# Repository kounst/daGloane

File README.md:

daGloane
========

daGloane is a quadcopter with a takeoff mass of less than 30grams

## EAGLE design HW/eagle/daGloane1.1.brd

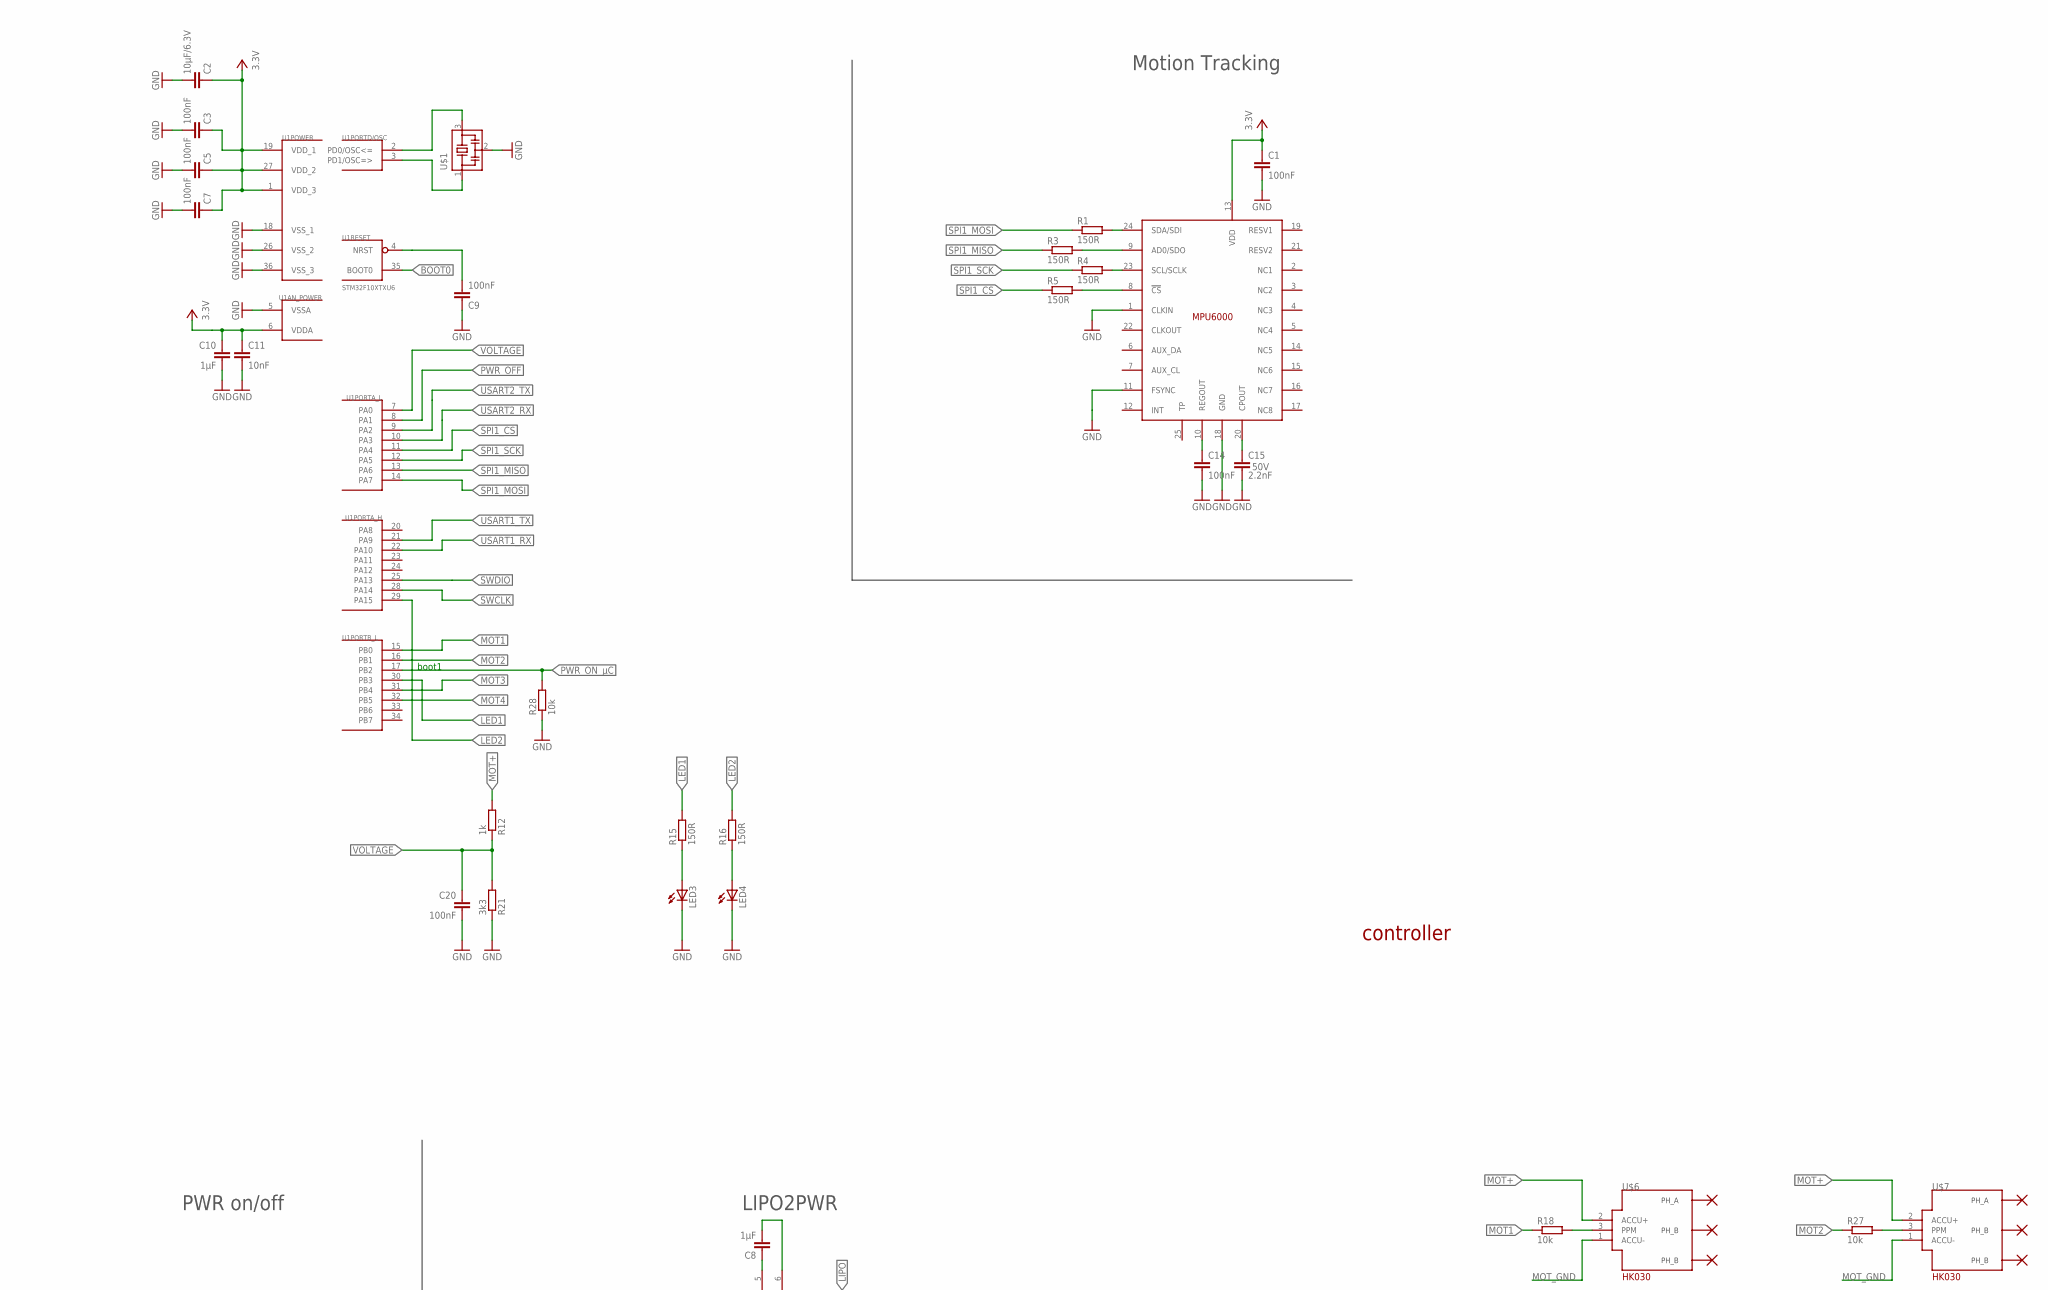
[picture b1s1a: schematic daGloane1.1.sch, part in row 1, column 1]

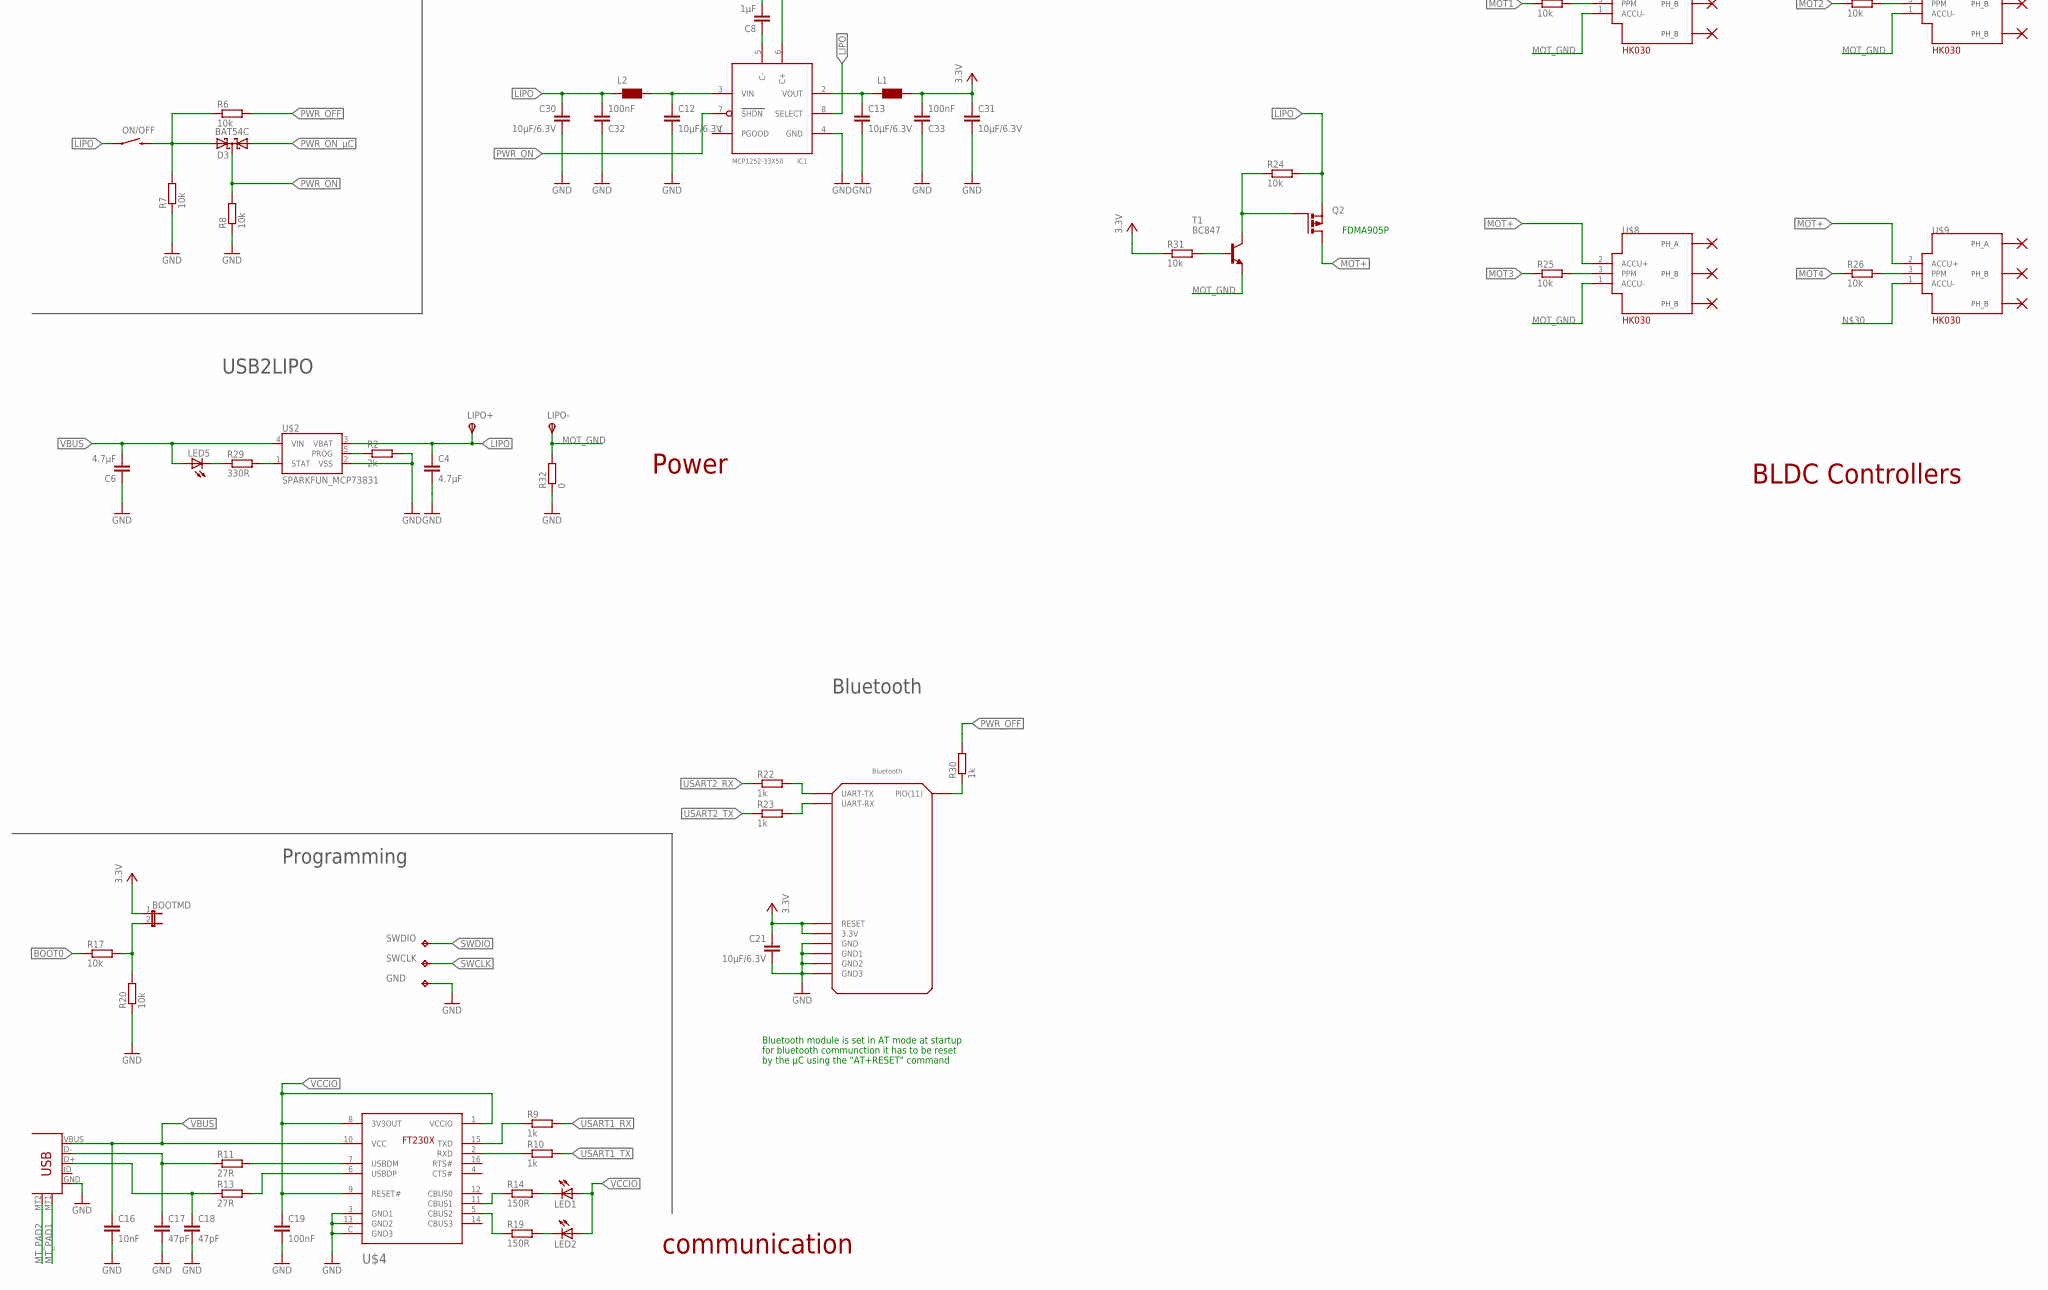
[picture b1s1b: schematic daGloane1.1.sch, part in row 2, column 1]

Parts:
BOOTMD: JUMPER-2; 1X02_50MIL
C1, C3, C5, C7, C9, C14, C19, C20, C32, C33: 100nF; C0603
C2, C12, C13, C21, C30, C31: 10µF/6.3V; C0805
C4, C6: 4.7µF; C0603
C8, C10: 1µF; C0603
C11, C16: 10nF; C0603
C15: 2.2nF; C0603; VOLTAGE 50V
C17, C18: 47pF; C0603
D3: BAT54C; SOT23
GND: TESTPAD_TPB1,27; TESTPAD_B1,27
IC1: MCP1252-33X50; MSOP8
L1, L2: WUERTH-ELEKTRONIK_WE-KI_0805_B
LED1, LED2, LED3, LED4, LED5: LEDCHIPLED_0603; CHIPLED_0603
LIPO+: TPSPAD1-13; P1-13
LIPO-: TPSPAD1-13; P1-13
ON/OFF: SWITCH-MOMENTARY-2SMD; TACTILE_SWITCH_SMD
Q2: P-MOSFET-SO8; MICROFET2X2
R1, R3, R4, R5, R14, R15, R16, R19: 150R; R0603
R2: 2k; R0603
R6, R7, R8, R17, R18, R20, R24, R25, R26, R27, R28, R31: 10k; R0603
R9, R10, R12, R22, R23, R30: 1k; R0603
R11, R13: 27R; R0603
R21: 3k3; R0603
R29: 330R; R0603
R32: 0; R0603
SWCLK: TESTPAD_TPB1,27; TESTPAD_B1,27
SWDIO: TESTPAD_TPB1,27; TESTPAD_B1,27
T1: BC847; SOT23
U1: STM32F10XTXU6; VFQFPN36
U$1: MURATA-FILTER_CSTCE__G
U$2: SPARKFUN_MCP73831; SPARKFUN_SOT23-5
U$3: MPU6000
U$4: SERIAL_FT230XQ; SERIAL_QFN4X4-16
U$5: BLUETOOTH_REDUCED
U$6, U$7, U$8, U$9: 3A_BLDC_CONTROLLER
X2: USB_MICROB_PLUG_MT; SPARKFUN-CONNECTORS_USB-MICROB

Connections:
BOOT0: R17.1, U1.35 (BOOT0)
D+: C18.1, R13.1, X2.D+
D-: C17.1, R11.1, X2.D-
GND: C1.2, C2.2, C3.2, C4.2, C5.2, C6.1, C7.2, C9.1, C10.2, C11.2, C12.2, C13.2, C14.2, C15.2, C16.2, C17.2, C18.2, C19.2, C20.2, C21.2, C30.2, C31.2, C32.1, C33.1, GND.PP, IC1.4 (GND), LED3.C, LED4.C, R2.2, R7.1, R8.1, R20.1, R21.1, R28.1, R32.1, U1.5 (VSSA), U1.18 (VSS_1), U1.26 (VSS_2), U1.36 (VSS_3), U$1.2, U$2.2 (VSS), U$3.1 (CLKIN), U$3.11 (FSYNC), U$3.18 (GND), U$4.3 (GND1), U$4.13 (GND2), U$4.C (GND3), U$5.P$13 (GND), U$5.P$14 (GND1), U$5.P$21 (GND2), U$5.P$22 (GND3), X2.GND
LED1: R15.2, U1.30 (PB3)
LED2: R16.2, U1.29 (PA15)
LIPO: C4.1, C30.1, C32.2, IC1.8 (SELECT), L2.2 (1), LIPO+.TP, ON/OFF.1, Q2.P$4 (S), Q2.P$7 (S), R24.2, U$2.3 (VBAT)
MOT1: R18.1, U1.15 (PB0)
MOT2: R27.1, U1.16 (PB1)
MOT3: R25.1, U1.31 (PB4)
MOT4: R26.1, U1.32 (PB5)
MOT+: Q2.P$1 (D), Q2.P$2 (D), Q2.P$5 (D), Q2.P$6 (D), Q2.P$8 (D), R12.2, U$6.2 (ACCU+), U$7.2 (ACCU+), U$8.2 (ACCU+), U$9.2 (ACCU+)
MOT_GND: LIPO-.TP, R32.2, T1.2 (E), U$6.1 (ACCU-), U$7.1 (ACCU-), U$8.1 (ACCU-)
MT_PAD1: X2.MT1 (MTN1)
MT_PAD2: X2.MT2 (MTN2)
unnamed: LED2.C, R19.2
unnamed: U1.2 (PD0/OSC<=), U$1.3
unnamed: R2.1, U$2.5 (PROG)
unnamed: R5.2, U$3.8 (!CS)
unnamed: C15.1, U$3.20 (CPOUT)
unnamed: C14.1, U$3.10 (REGOUT)
unnamed: R22.2, U$5.P$1 (UART-TX)
unnamed: LED3.A, R15.1
unnamed: LED4.A, R16.1
unnamed: BOOTMD.2, R17.2, R20.2
unnamed: R14.1, U$4.11 (CBUS1)
unnamed: R19.1, U$4.5 (CBUS2)
unnamed: R4.2, U$3.23 (SCL/SCLK)
unnamed: LED1.C, R14.2
unnamed: R23.2, U$5.P$2 (UART-RX)
unnamed: R11.2, U$4.7 (USBDM)
unnamed: R13.2, U$4.6 (USBDP)
unnamed: R3.2, U$3.9 (AD0/SDO)
unnamed: R1.2, U$3.24 (SDA/SDI)
unnamed: R9.1, U$4.15 (TXD)
unnamed: R10.1, U$4.2 (RXD)
unnamed: R18.2, U$6.3 (PPM)
unnamed: D3.2 (A2), ON/OFF.3 (2), R6.1, R7.2
unnamed: C8.2, IC1.6 (C+)
unnamed: U1.3 (PD1/OSC=>), U$1.1
unnamed: R30.1, U$5.P$34 (PIO(11))
unnamed: Q2.P$3 (G), R24.1, T1.3 (C)
unnamed: C8.1, IC1.5 (C-)
unnamed: R31.2, T1.1 (B)
unnamed: R27.2, U$7.3 (PPM)
unnamed: R25.2, U$8.3 (PPM)
unnamed: R26.2, U$9.3 (PPM)
unnamed: R29.2, U$2.1 (STAT)
unnamed: LED5.C, R29.1
unnamed: C12.1, IC1.3 (VIN), L2.1 (2)
unnamed: C13.1, IC1.2 (VOUT), L1.2 (1)
PWR_OFF: R6.2, R30.2, U1.8 (PA1)
PWR_ON: D3.3 (CC), IC1.7 (SHDN), R8.2
PWR_ON_µC: D3.1 (A1), R28.2, U1.17 (PB2)
RESET1: C9.2, U1.4 (NRST)
SPI1_CS: R5.1, U1.11 (PA4)
SPI1_MISO: R3.1, U1.13 (PA6)
SPI1_MOSI: R1.1, U1.14 (PA7)
SPI1_SCK: R4.1, U1.12 (PA5)
SWCLK: SWCLK.PP, U1.28 (PA14)
SWDIO: SWDIO.PP, U1.25 (PA13)
USART1_RX: R9.2, U1.22 (PA10)
USART1_TX: R10.2, U1.21 (PA9)
USART2_RX: R22.1, U1.10 (PA3)
USART2_TX: R23.1, U1.9 (PA2)
VBUS: C6.2, C16.1, LED5.A, U$2.4 (VIN), U$4.10 (VCC), X2.VBUS
VCC: BOOTMD.1, C1.1, C2.1, C3.1, C5.1, C7.1, C10.1, C11.1, C21.1, C31.1, C33.2, L1.1 (2), R31.1, U1.1 (VDD_3), U1.6 (VDDA), U1.19 (VDD_1), U1.27 (VDD_2), U$3.13 (VDD), U$5.P$11 (RESET), U$5.P$12 (3.3V)
VCCIO: C19.1, LED1.A, LED2.A, U$4.1 (VCCIO), U$4.8 (3V3OUT), U$4.9 (RESET#)
VOLTAGE: C20.1, R12.1, R21.2, U1.7 (PA0)

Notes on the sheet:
FT230X
boot1
Power
communication
controller
Programming
Bluetooth
LIPO2PWR
USB2LIPO
PWR on/off
Motion Tracking
BLDC Controllers
Bluetooth module is set in AT mode at startup
for bluetooth communction it has to be reset
by the µC using the "AT+RESET" command
FDMA905P

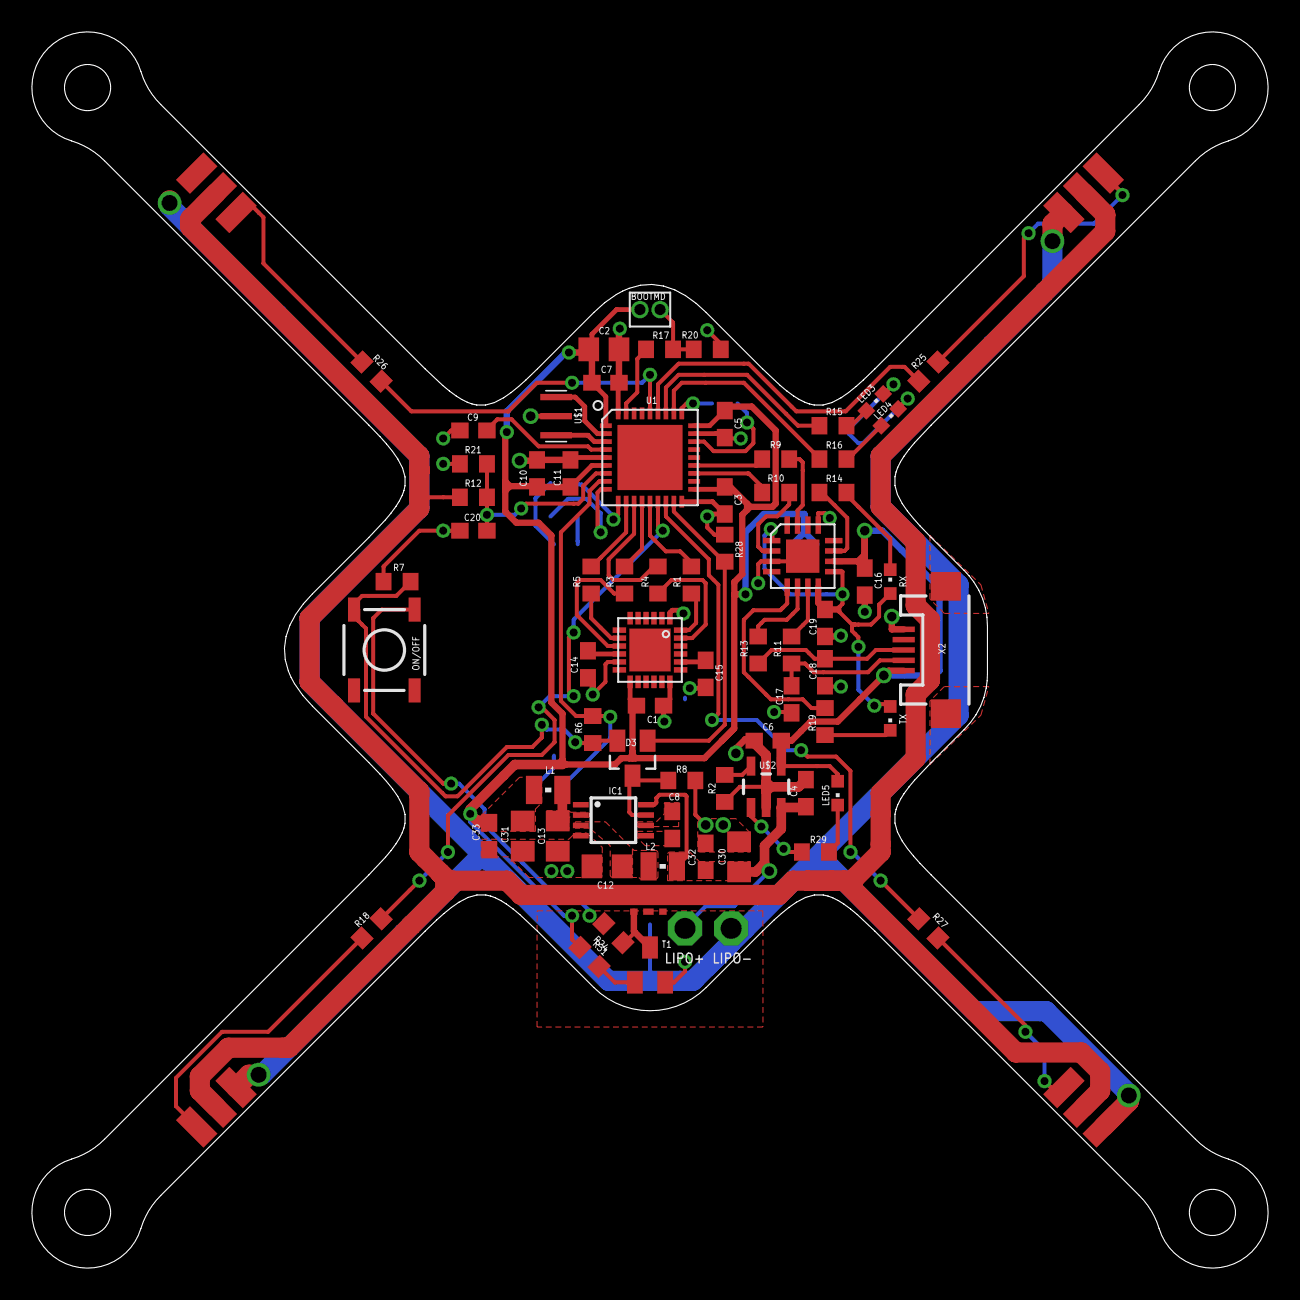
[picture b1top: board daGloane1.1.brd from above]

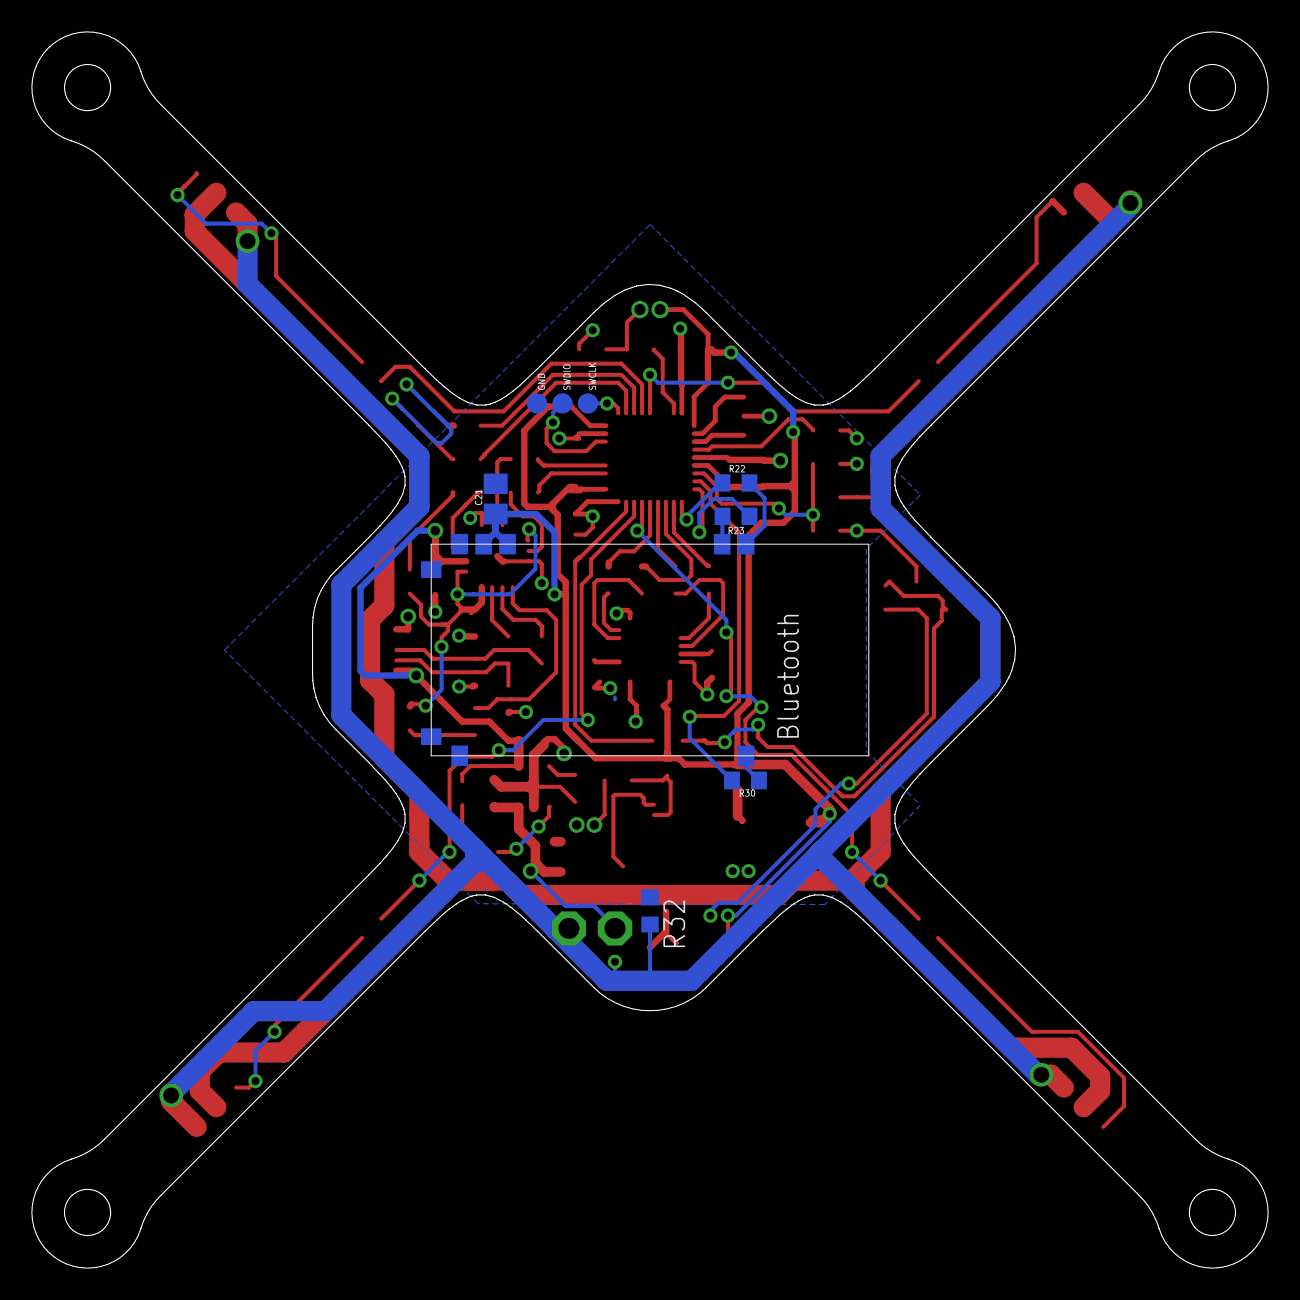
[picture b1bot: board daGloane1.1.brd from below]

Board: 2 copper layers, 77.7 x 77.7 mm, 87 parts (9 on the bottom side), 67 nets.

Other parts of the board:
U$11: DAGLOANE_LOGO

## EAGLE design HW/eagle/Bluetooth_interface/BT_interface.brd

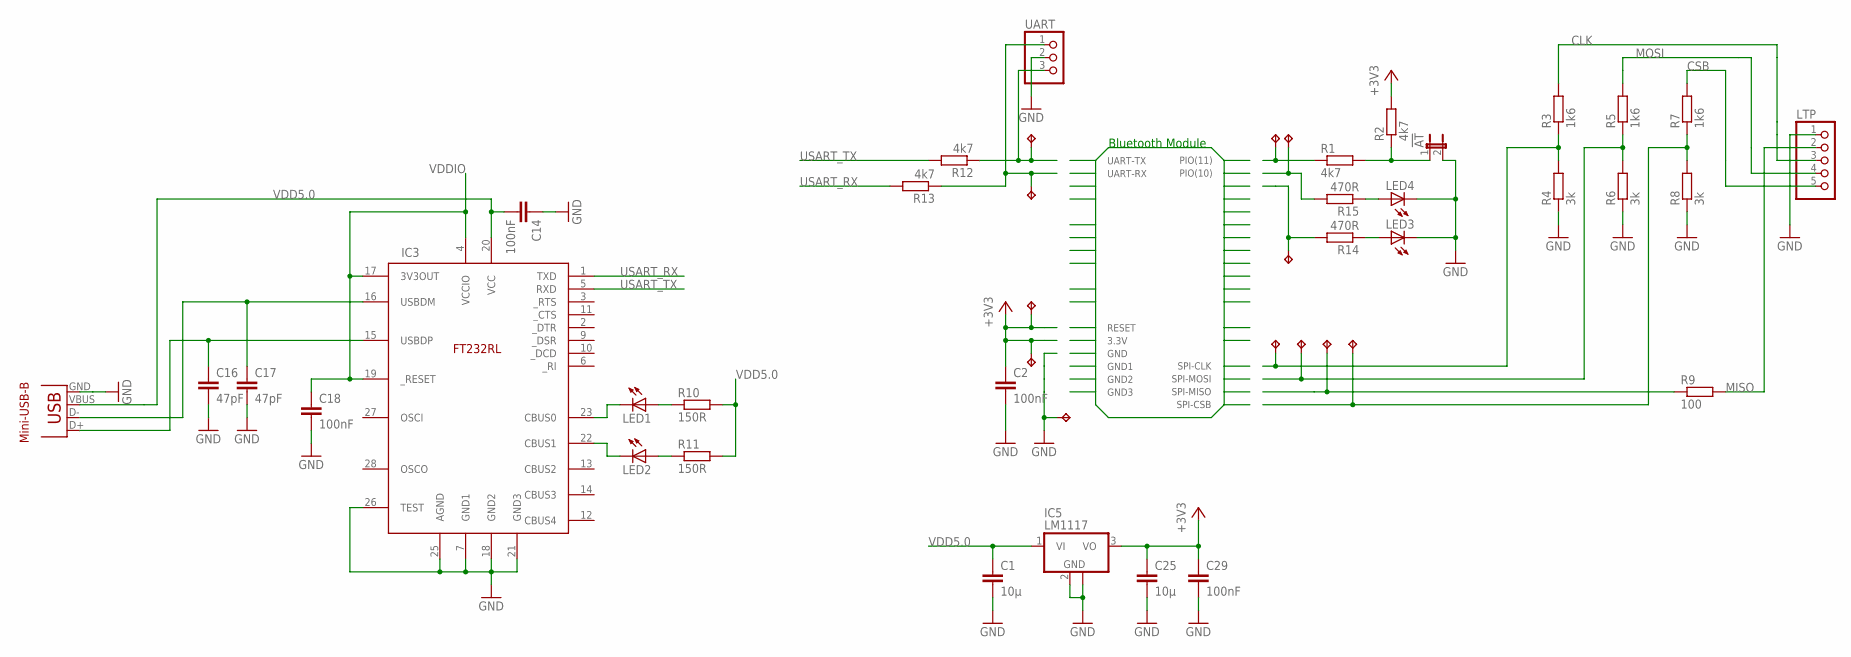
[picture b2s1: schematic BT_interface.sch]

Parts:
!AT: JUMPER-2PTH; 1X02
C1, C25: 10µ; C0805
C2, C14, C18, C29: 100nF; C0805
C16, C17: 47pF; C0805
IC3: FT232RL; SSOP28DB
IC5: UA78M05DCY; SOT223
LED1, LED2, LED3, LED4: LEDCHIPLED_0603; CHIPLED_0603
LTP: PINHD-1X5; 1X05
R1, R2, R12, R13: 4k7; R0805
R3, R5, R7: 1k6; R0805
R4, R6, R8: 3k; R0805
R9: 100; R0805
R10, R11: 150R; R0805
R14, R15: 470R; R0805
U$2, U$3, U$4, U$5, U$6, U$7, U$8, U$9, U$10, U$11, U$12, U$13: SPRING_HEADER
UART: PINHD-1X3; 1X03
USB1: USB-MB-S2; USB-MP-S2

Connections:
+3V3: C2.1, C25.1, C29.1, IC5.3 (VO), R2.2, U$4.P$1, U$5.P$1
CLK: LTP.3, R3.2
CSB: LTP.5, R7.2
D+: C16.1, IC3.15 (USBDP), USB1.D+
D-: C17.1, IC3.16 (USBDM), USB1.D-
GND: !AT.2, C1.2, C2.2, C14.1, C16.2, C17.2, C18.2, C25.2, C29.2, IC3.7 (GND1), IC3.18 (GND2), IC3.21 (GND3), IC3.25 (AGND), IC3.26 (TEST), IC5.2 (GND), IC5.4 (GND), LED3.C, LED4.C, LTP.1, R4.1, R6.1, R8.1, U$6.P$1, UART.2, USB1.GND
MISO: LTP.2, R9.2
MOSI: LTP.4, R5.2
unnamed: R1.1, U$9.P$1
unnamed: IC3.23 (CBUS0), LED1.C
unnamed: IC3.22 (CBUS1), LED2.C
unnamed: LED1.A, R10.1
unnamed: LED2.A, R11.1
unnamed: !AT.1, R1.2, R2.1
unnamed: R7.1, R8.2, U$11.P$1
unnamed: R5.1, R6.2, U$7.P$1
unnamed: R3.1, R4.2, U$8.P$1
unnamed: R12.1, U$2.P$1, UART.3
unnamed: R13.1, U$3.P$1, UART.1
unnamed: LED3.A, R14.1
unnamed: LED4.A, R15.1
unnamed: R14.2, U$13.P$1
unnamed: R9.1, U$10.P$1
unnamed: R15.2, U$12.P$1
USART_RX: IC3.1 (TXD), R13.2
USART_TX: IC3.5 (RXD), R12.2
VDD5.0: C1.1, C14.2, IC3.20 (VCC), IC5.1 (VI), R10.2, R11.2, USB1.VBUS
VDDIO: C18.1, IC3.4 (VCCIO), IC3.17 (3V3OUT), IC3.19 (_RESET)

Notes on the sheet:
FT232RL
Mini-USB-B
UART-TX
UART-RX
RESET
3.3V
GND
GND1
GND2
GND3
SPI-CSB
SPI-MISO
SPI-MOSI
SPI-CLK
PIO(11)
PIO(10)
Bluetooth Module

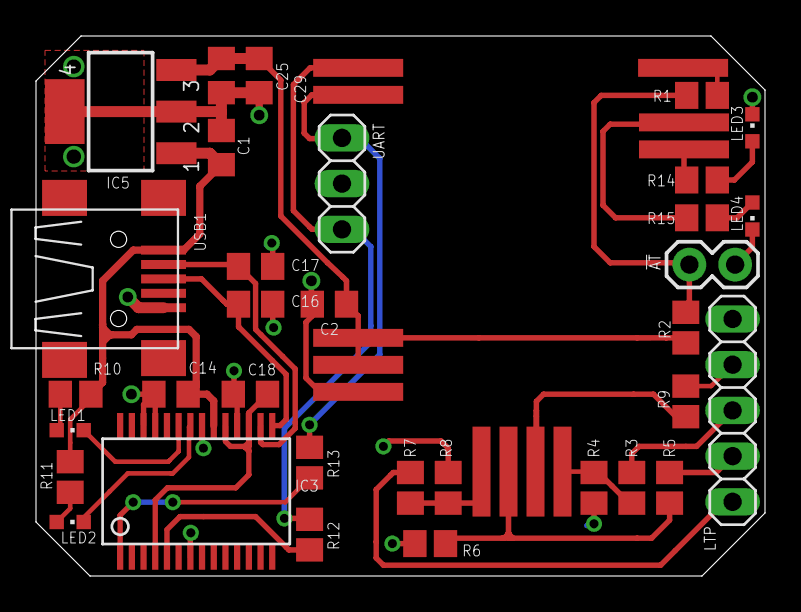
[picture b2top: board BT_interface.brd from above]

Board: 2 copper layers, 40.5 x 30.0 mm, 45 parts (0 on the bottom side), 28 nets.

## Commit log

2012-07-07 DC/DC layout done
2012-07-08 layout of center piece is done!
2012-07-08 package added to HK03 BLDC controller library
2012-07-08 testpads replaced with HK03 bldc controller symbol & package
2012-07-08 routing completed!! optimization pending
2012-07-08 orientation of BLDC controllers changed
2012-07-08 GND shape outline changed
2012-07-08 estimation of the total weight of daGloane
2012-07-10 RefDesignators position rearranged
2012-07-11 DC/DC layout improved
2012-07-11 RefDesignator rearranged
2012-07-11 DRC error resolved
2012-07-11 error in schematic fixed: Wrong pin of MPU6000 connected to GND
2012-07-13 Update BLDC
2012-07-15 - micro usb connector with electrical connection to mounting pad added - micro usb connector replaced with new part - micro usb connectors mounting pads' size increased with shape. This is to increas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
2012-07-15 hole diameter for mounting of the motors changed. 2.95mm to 2.90mm
2012-07-15 inital commit of draft "daGloane" logo
2012-07-15 it looks way better now..
2012-07-15 inital commit of logo png
2012-07-15 white filling of ellipses changed to transparent
2012-07-15 resolution increased
2012-07-15 usb connectors added
2012-07-15 image added
2012-07-15 minor change
2012-07-15 reset to previous state
2012-07-16 line width increased
2012-07-19 new perspective logo
2012-07-21 daGloane logo added to library
2012-07-21 logo placed on pcb
2012-07-21 trace angles fixed
2012-07-29 changed connection of the bluetooth module's AT pin.
    It is now connected to the pwr_on/off logic. This will set it into AT mode at startup so the µC can configure the module. Once the configuration is done the µC can set it into operating mode by simpl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
2012-07-29 updated to version in lbr
2012-07-29 removed
2012-07-30 initial commit of BT interface PCB
2012-07-30 labels changed, parts smashed, labels resized and rearranged
2012-07-30 layout finished
2012-07-30 footprint for spring loaded header added
2012-07-31 added status LED
2012-07-31 parts rearranged to leave more space for BT module
2012-07-31 Reference Designators resized rearranged
2012-08-12 bluetooths footprint corrected to actual dimensions
2012-08-12 bluetooth module replaced with new version
2012-08-12 bluetooth module footprint corrected to match actual dimensions
2012-08-12 bluetooth module footprint removed and replaced with dummy drawing
2012-08-12 stm32 vqfpn36 package cream layer divided in 4 segments
2012-08-12 gnd shape slightly changed
2012-08-12 initial commit daGlaone panelized
2012-08-13 changed some values
2012-08-13 resistor values for LEDs changed back; voltage drop over LEDs at 10mA is 2V. Therefore the voltage drop accross the resistor has to be 1.3V (3.3V supply) --> R = 1.3V / 10mA = 130Ohm; next E12 value 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
2012-08-15 initial commit of gerber files
2012-08-17 silkscreen of STM32 and FT230 modified
2012-08-17 silkscreen of stm32 and FT230 modified outline of maximum usable boadspace in eagle freeware version removed
2012-08-18 minor changes
2012-08-20 gerber data for daGlaone and BTinterface
2012-08-20 font type changed to vector
2012-09-16 motor mounting holes diamenters changed to 3.4mm
2012-09-22 initial commit of daGloane firmware. This is code for testing only - no actual functionality
2012-09-22 PWM testcode implemented
2012-10-13 -spi reading from the MPU-6000 is now working (polling mode) -single byte read -continous reading of several bytes - UART command line interface implemented -this was done my using a library by Thoma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
2012-10-13 missing files for SPI and serial command interface (uAC) added string compare function in uAC changed to be case insensitive
2012-10-14 compile switch added to make uac's string compare case insensitive
2012-10-14 unused code removed
2012-10-14 uac message is now sent before daGloane turns itself off
2012-10-14 all data of the MPU-6000 can now be read over the uac interface
2012-10-15 Bit manipulation of data read ofer SPI replaced with union This made it necessary to change the order of high and low byte read from the SPI.
2012-10-20 uAC command handler moved to a seperate file
2012-10-20 header comment changed to look more like the other files comments
2012-10-20 SysTick timer related functions move from main.c to this files
2012-10-20 some functions and prototypes move to other source and header files
2012-10-20 typedef and function prototypes move from main.c to this file
2012-10-20 initial commit of an implementation of the kalman filter. This is completely untested
2012-10-20 we don't really need this..
2012-10-20 printf did't work properly for float smaller than 0 and bigger than -1 This bug fix is untested
2012-10-20 uAC command attach function created
2012-10-20 power button handling moved to seperate funciton in GPIO.c
2012-10-20 missing include of TIM.h added
2012-10-20 #endif statement moved to right location
2012-10-20 several commands moved to seperate functions some comments added
2012-10-23 added TIM.h for Delay function required
2012-10-24 mpu data typedef changed back to previous state
2012-10-25 Remapping of JTAG pins activated. Initialization of LED and PWM3 IOs fixed
2012-10-25 HeartBeat function added
2012-10-25 Heatbeat function added
2012-10-25 this source file implements Consistent Overhead Byte Stuffing. This will be used for the UART communication over the BT module
2012-11-02 prototypes for SPI1_read() and SPI_writebyte() functions added
2012-11-02 SPI1_writebyte() function added
2012-11-02 new uac command added. The command "mpu" allows you to read from or write to a register of the mpu using the command line interface
2012-11-05 disciption of the uart message protocoll to be used by daGloane for communication over BT interface
2012-11-07 PWM update function implemented uac function to set PWM duty-cycle implemented
2012-11-08 heart beat led now fades on and off with a 0.5Hz frequency
2012-11-08 LED fading can be controled with a uac command
2012-11-08 mapping of data in union replaced with function that does bitshifting. This just makes to code way easier to read.
2012-11-11 kalman filter activated for testing
2012-11-11 incorrect mapping of data in MPU_read function fixed
2012-11-11 function for kalman filter tuning implemented
2012-11-17 experimental implementation of bluetooth transmit routines
2012-11-23 scaling of temperatur data provided by mpu-6000 done
2012-11-23 new uac commands: - changing of baudrate uart connected to BT module - sending of data to the BT module
2012-11-23 handler for data received from the BT module implemented
2012-11-23 UART2 enabled for communication with the BT module
2012-11-23 configuration of UART2 for BT communication
2012-11-23 changed length informated that is send along with message to the total number of bytes
2012-11-23 uac command implemented that alows to make the copter send messages over the BT interface
2012-11-25 cobs encoding function added that modifies the input byte array instead of storing the output string to a seperate array
2012-11-25 private function prototypes moved from header to source file calls of alloca function removed
2012-11-25 both LEDs are now turned on in case of an hard fault
2012-11-25 uac command btmsg implementation changed to be more versatile
2012-12-02 New version of daGloane HW. - There is almost no current consumption when turned off. Its not necessary to disconnect battery anymore.
2013-03-10 PWM frequency changed 333Hz 3ms
2013-03-10 help string changed to reflect changes made to PWM
2013-03-10 rotation of gyro signals to prop coordinate system (rotation in z axis by 45 degree) implemented
2013-03-10 code formating; no functional change
2013-03-16 order of channels in BT_message mapping to local variable corrected
2013-03-16 uac command for reading back the pwm values implemented
2013-03-16 bytes that are received via bluetooth are no longer transfered over the uac debugging interface
2013-03-16 gyro data are no longer transmitted via bluetooth interface on uart 2
2013-03-16 initial commit of the daGloane Remote
    The target is to make the daGloane qaudcopter controlable using a Android Smartphone.
    For now to ease devolempent a common RC remote control will be used.
    daGloane Remote is a stm32 discovery eval board and a bluetooth interface that can be connected to a RC remote control. It will read the PPM signal of the remote and transfer the channel information 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
2013-03-16 what is daGloane_remote
2013-03-17 AT communication is now handled in a FSM
2013-09-06 comment changed to make a difference
2013-09-09 Controller and Filter in Simulink. Looking for building a C model via Matlab
2013-09-10 simulink modell
2013-09-10 Erste Version des auf C konvertierten Simulink Codes
2013-09-16 correct signal names discrete int and derivate new c code generated
2013-09-16 new version
2013-09-16 model version 1.14
2013-09-16 initial commit of the daGloane Android remote app
2013-09-16 daGloane fw project zip
2013-09-19 project workspace zip
2013-09-23 software from 23.09.2013. problem in main.c while loop. seems like looping only one time/or 0.
2013-10-06 data collected testing the complementary filter
2013-10-08 neue dateien
2013-10-08 Systick clock frequency changed to 250Hz
2013-10-08 uac command "getpwm" now returns the Motor pwm instead of the remote control pwm signals
2013-10-08 functions for uart dma data transfer added
2013-10-08 tigger flag for main loop execution added; this flag is set in the systick interrupt and is reset in the main loop
2013-10-08 main loop is only being executed if the tigger flag is set; the trigger flag is set by the systick interrupt which is fired at a rate of 250Hz
2013-10-22 22.10. new C Code from simulink model
2013-10-22 for quad model
2013-11-12 new c code
2013-11-14 pid values can now be changed via bluetooth
2021-02-15 step file of pcb added
2021-02-17 Programming fixture added
2021-02-18 Programming fixture improved
2021-02-20 migration of copter FW platformio started
2021-03-01 migration to platfromio and STM32Cube libraries made
2021-03-01 unneded files removed
2021-03-01 kicad converted eagle project added
2021-03-05 complementary filter implementation started
2021-03-14 MPU read is triggered by TIM2 update interrupt now. Main loop runs after SPI communication is done.
